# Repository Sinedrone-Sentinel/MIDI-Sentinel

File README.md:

This is the Midi-Sentinel Project

A midi controller with BOTH a joystick AND a thumbstick.
However, you are not limited to JUST these 2 XY controls.
You can have 2 Joysticks, or 2 thumbsticks or any combination
that you wish. You only need to modify the project to your needs.

BEFORE YOU START BUYING PARTS
The LCD screen and the Mainboard ARE DIFFERENT SIZES on 
prototype B than they are on prototype A. Make sure that the
filename prefixes MATCH in your LOCAL folder copy before you
start spending money!

In the DIY section, you will find "How-To" guides to build the
Midi Sentinel, step-by-step for each version of the Midi-Sentinel.
Along with separate parts lists for each version that includes
the original purchase source. (No guarantee that any particular
part will still be in stock on sites listed.)

In the Images section, you will find pictures of the different
versions so you know what you are looking for in the other sections.

In the CAD section, you will find the files for the early prototype
and the final Kickstarter version. The early kickstarter version
will be cheaper to make considering that the enclosure used was
NOT a custom designed enclosure, but an off the shelf enclosure
that you can buy online for around $20.
Also, worth noting. If you buy the "Off-the-shelf" enclosure, there
is NO usb mounting "hole" on the back. You will either need to cut
that out yourself or the website where it is sold has a fairly cheap
machining option where they will modify it for you before shipping.

In the EDA section, you will find the mainboard circuit board design
file and the knob controller circuit board file.  These can be uploaded
as they are to sites like PCBWay.com to be manufactured for about $5
per board. (Be aware though, PCBWay has a 5 board minimum per schematic.)

If you are here, it is because you are interested in either building
your own (DIY kit or self sourcing parts) or you want to modify the
one you have. Either way here is a short list of basic tools and
items that you should have before you start.

Soldering Iron, Solder, Flux pen or paste, spare wire, multimeter,
philips head screw driver, wire cutters, wire brush (for cleaning soldering iron)

Other tools may be required depending on what you are attempting.

Software needed, Arduino IDE.

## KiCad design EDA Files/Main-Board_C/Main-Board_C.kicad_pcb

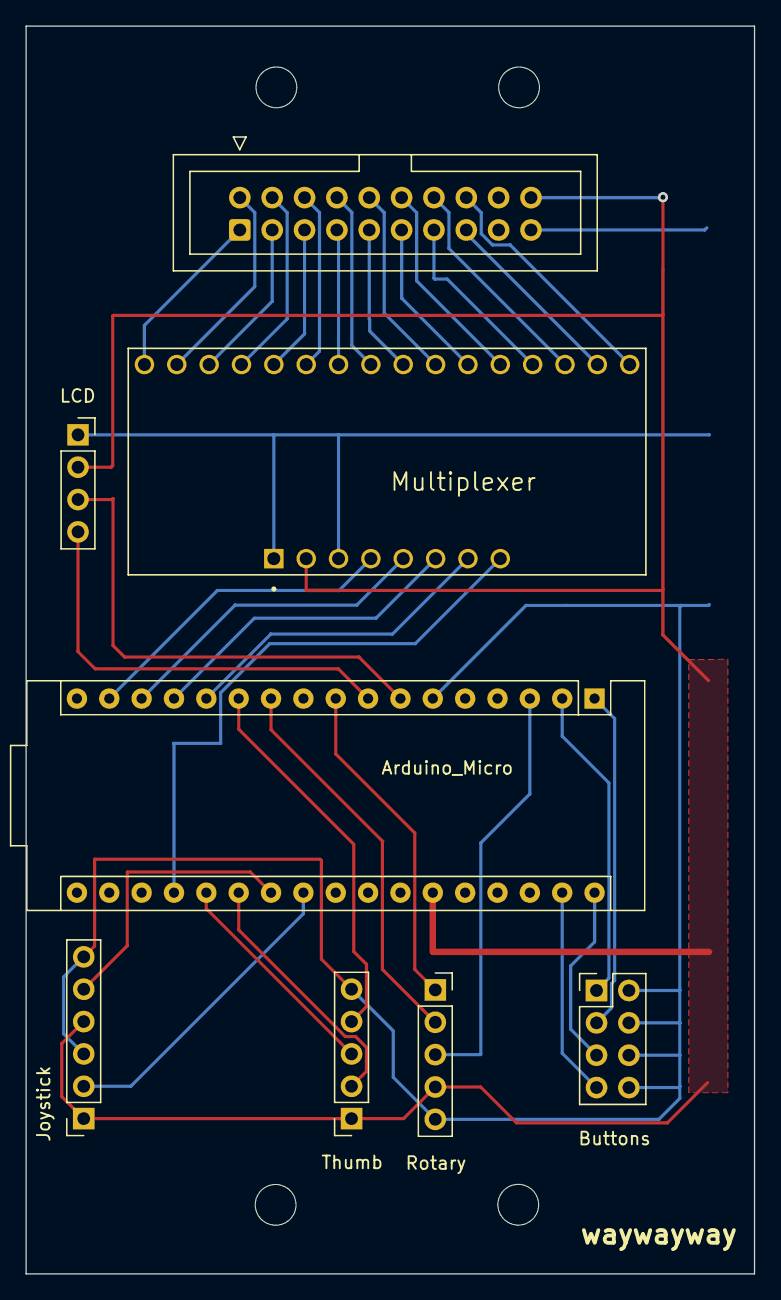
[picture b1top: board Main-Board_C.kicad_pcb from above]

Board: 2 copper layers, 57.2 x 98.0 mm, 8 parts (0 on the bottom side), 37 nets.

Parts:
BOB-1: Multiplexer; BOB-09056
IDC1: 16_Pin_IDC_2x08_Power; IDC-Header_2x10_P2.54mm_Vertical
J1: Buttons; PinHeader_2x04_P2.54mm_Vertical
J4: Rotary; PinSocket_1x05_P2.54mm_Vertical
J9: LCD; PinSocket_1x04_P2.54mm_Vertical
J10: Thumb; PinSocket_1x05_P2.54mm_Vertical
J11: Joystick; PinSocket_1x06_P2.54mm_Vertical
U1: Arduino_Micro

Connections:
+5V: BOB-1.JP3-2 (VCC), IDC1.20, J4.4, J9.2, J10.1, J11.1, J11.4, U1.29 (+5V)
GND: BOB-1.JP3-1 (GND), BOB-1.JP3-3 (EN), IDC1.19, J1.2, J1.4, J1.6, J1.8, J4.5, J9.1, J10.5, J11.3, J11.6, U1.6 (GND)
unnamed: BOB-1.JP1-1 (C0), IDC1.1
unnamed: BOB-1.JP1-2 (C1), IDC1.2
unnamed: BOB-1.JP1-3 (C2), IDC1.3
unnamed: BOB-1.JP1-4 (C3), IDC1.4
unnamed: BOB-1.JP1-5 (C4), IDC1.5
unnamed: BOB-1.JP1-6 (C5), IDC1.6
unnamed: BOB-1.JP1-7 (C6), IDC1.7
unnamed: BOB-1.JP1-8 (C7), IDC1.8
unnamed: BOB-1.JP1-9 (C8), IDC1.9
unnamed: BOB-1.JP1-10 (C9), IDC1.10
unnamed: BOB-1.JP1-11 (C10), IDC1.11
unnamed: BOB-1.JP1-12 (C11), IDC1.12
unnamed: BOB-1.JP1-13 (C12), IDC1.13
unnamed: BOB-1.JP1-14 (C13), IDC1.14
unnamed: BOB-1.JP1-15 (C14), IDC1.15
unnamed: BOB-1.JP1-16 (C15), IDC1.16
unnamed: BOB-1.JP3-8 (COM), U1.21 (A0/D18)
unnamed: BOB-1.JP3-4 (S0), U1.16 (~D11)
unnamed: BOB-1.JP3-5 (S1), U1.15 (~D10/A10)
unnamed: BOB-1.JP3-6 (S2), U1.14 (~D9/A9)
unnamed: BOB-1.JP3-7 (S3), U1.13 (D8/A8)
unnamed: J10.3, U1.22 (A1/D19)
unnamed: J10.2, U1.23 (A2/D20)
unnamed: J11.5, U1.24 (A3/D21)
unnamed: J11.2, U1.25 (A4/D22)
unnamed: J4.3, U1.3 (D1/TX)
unnamed: J9.3, U1.7 (D2/SDA)
unnamed: J4.1, U1.9 (D4/A6)
unnamed: J10.4, U1.12 (D7)
unnamed: J1.7, U1.33 (D14)
unnamed: J1.5, U1.34 (D15)
unnamed: J1.3, U1.1 (D16)
unnamed: J1.1, U1.2 (D17)
unnamed: J9.4, U1.8 (~D3/SCL)
unnamed: J4.2, U1.11 (~D6/A7)

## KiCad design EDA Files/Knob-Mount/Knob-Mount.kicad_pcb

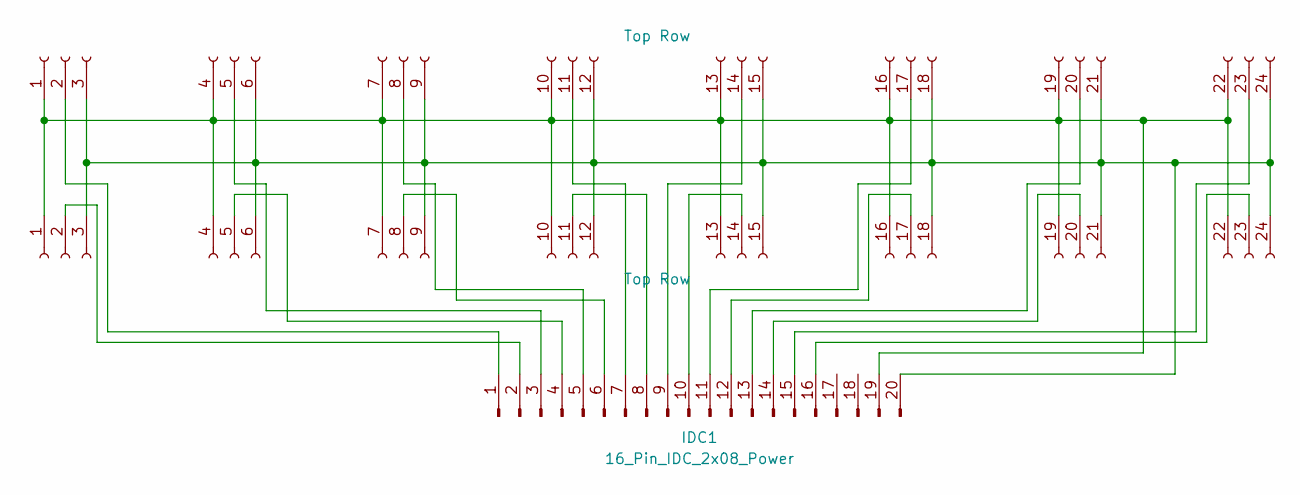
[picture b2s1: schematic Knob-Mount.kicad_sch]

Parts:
IDC1: 16_Pin_IDC_2x08_Power; IDC-Header_2x10_P2.54mm_Vertical
J1, J2: Top Row; PinHeader_8x3_P2.54mm_Knobs

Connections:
unnamed: IDC1.1, J1.2
unnamed: IDC1.2, J2.2
unnamed: IDC1.3, J1.5
unnamed: IDC1.4, J2.5
unnamed: IDC1.5, J1.8
unnamed: IDC1.6, J2.8
unnamed: IDC1.7, J1.11
unnamed: IDC1.8, J2.11
unnamed: IDC1.9, J1.14
unnamed: IDC1.10, J2.14
unnamed: IDC1.11, J1.17
unnamed: IDC1.12, J2.17
unnamed: IDC1.13, J1.20
unnamed: IDC1.14, J2.20
unnamed: IDC1.15, J1.23
unnamed: IDC1.16, J2.23
unnamed: IDC1.19, J1.1, J1.4, J1.7, J1.10, J1.13, J1.16, J1.19, J1.22, J2.1, J2.4, J2.7, J2.10, J2.13, J2.16, J2.19, J2.22
unnamed: IDC1.20, J1.3, J1.6, J1.9, J1.12, J1.15, J1.18, J1.21, J1.24, J2.3, J2.6, J2.9, J2.12, J2.15, J2.18, J2.21, J2.24

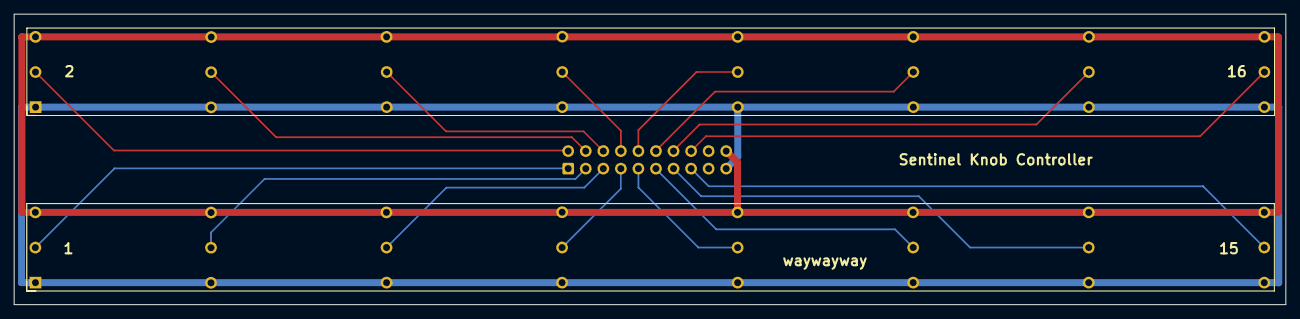
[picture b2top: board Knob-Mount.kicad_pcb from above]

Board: 2 copper layers, 184.0 x 42.0 mm, 3 parts (1 on the bottom side), 18 nets.

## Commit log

2024-03-26 Added Original Code File
    Original Midi-Sentinel Release Code. 16 knobs on a multiplexer, using an Arduino Micro, with a joystick, thumbstick, 16x2 LCD and push button rotary encoder.
2024-03-26 EDA Files
    Main Board and controller board designs
2024-03-26 EDA Upload
2024-03-27 Product Type A
    Upload of Original Prototype Image
2024-03-27 Product Images
    Various Prototype and Product Images
2024-03-27 added panels
    A and B panels
2024-03-27 Cad Files
    Enclosures for both prototypes
2024-03-27 upload read me
    Readme file
2024-03-27 Placeholder files
    Need to create files
2024-03-28 custom symbol
2024-03-31 update lists
2024-04-02 Update README.md
    Typo found ...
2024-04-02 Image update
2024-04-04 Update Midi_Sentinel.ino
    Applied the license as described in the License file itself.
2024-04-04 Update Midi_Sentinel.ino
    Licensing removed.
    5 other Github projects are being used in this code and those license references need to be made first.
2024-04-04 Parts lists update
2024-04-04 Complete EDA Update
2024-04-04 PCBWAY zip files added
2024-04-05 Revert "Applied license and added copyright info"
2024-04-06 Front Panel Blanks
